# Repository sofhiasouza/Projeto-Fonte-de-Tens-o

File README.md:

# Projeto Fonte de Tensão - Eletrônica para Computação - BCC 020 - ICMC- USP

Grupo:
 - [Ana Vitória Gouvea](mailto:anavitoria_gouvea@usp.br)
 - [Eduardo Amaral](https://rolimans.dev)
 - [Matheus Luis Oliveira](mailto:matheuslos@usp.br)
 - [Sofhia de Souza](mailto:sofhiasouza@usp.br)

Turma: 
    BCC 020

Disciplina:
    SSC0180 - Eletrônica para Computação

Docente responsável:
    Eduardo do Valle Simões

# Vídeo de apresentação do projeto:

# Lista de componentes do circuito:

- 1x  [Transformador Trafo 24V 1A - 110/220VAC](https://www.baudaeletronica.com.br/transformador-trafo-1a-24v.html)
- 4x [Diodo 1N4004](https://www.baudaeletronica.com.br/diodo-1n4004.html) (Ponte de diodos retificadora / MAX 400V - 1A)
- 1x [Capacitor 220uF - 35 V](https://www.baudaeletronica.com.br/capacitor-eletrolitico-220uf-35v.html)
- 1x [Led Azul](https://www.baudaeletronica.com.br/led-de-alto-brilho-azul.html) (Gastará aprox 5mA)
- 2x [Resistor 2k2](https://www.baudaeletronica.com.br/resistor-2k2-5-1-4w.html) (Fica em série com o LED e o - Potênciometro)
- 1x [Diodo Zener 13V - 0.5W](https://www.baudaeletronica.com.br/diodo-zener-bzx55c-13v-0-5w.html) (Recebe no máximo 0.3W)
- 1x [Resistor 2k](https://www.baudaeletronica.com.br/resistor-2k-5-1-4w.html) (Fica em série com o Zener)
- 1x [Potênciometro 5K](https://www.baudaeletronica.com.br/potenciometro-linear-de-5k-5000.html)
- 1x [Transistor NPN BC337](https://www.baudaeletronica.com.br/transistor-npn-bc337.html)
- 1x [Switch](https://www.baudaeletronica.com.br/chave-alavanca-mrs-101n-amarela-com-neon.html)

# Simulação do Circuito no simulador Falstad:

- Acesse o simulador [Falstad](https://falstad.com/circuit/circuitjs.html)
- Vá em `File > Import from Text` e cole o conteúdo do arquivo `./circuitoFalstad.txt` presente neste repositório.

A simulação aberta deve ser semelhante a esta:

# Esquemático do Circuito no software CAD Eagle:
 - Obtenha o software [Eagle](https://www.autodesk.com/products/eagle/blog/how-to-install-autodesk-eagle-on-windows-mac-and-linux/)
 - Vá em `File > Open > Schematic...` e selecione o arquivo `./EagleFiles/fonte_simoes.sch` presente neste repositório.

O esquemático aberto deve ser semelhante a este:

# PCB   do Circuito no software CAD Eagle:
 - Obtenha o software [Eagle](https://www.autodesk.com/products/eagle/blog/how-to-install-autodesk-eagle-on-windows-mac-and-linux/)
 - Vá em `File > Open > Board...` e selecione o arquivo `./EagleFiles/fonte_simoes.brd` presente neste repositório.

O PCB aberto deve ser semelhante a este:

# Licença
Este projeto é livre; você pode redistribuí-lo e/ou modificá-lo sobre os termos da GNU General Public License publicada pela Free Software Foundation; versão 3 ou superior.

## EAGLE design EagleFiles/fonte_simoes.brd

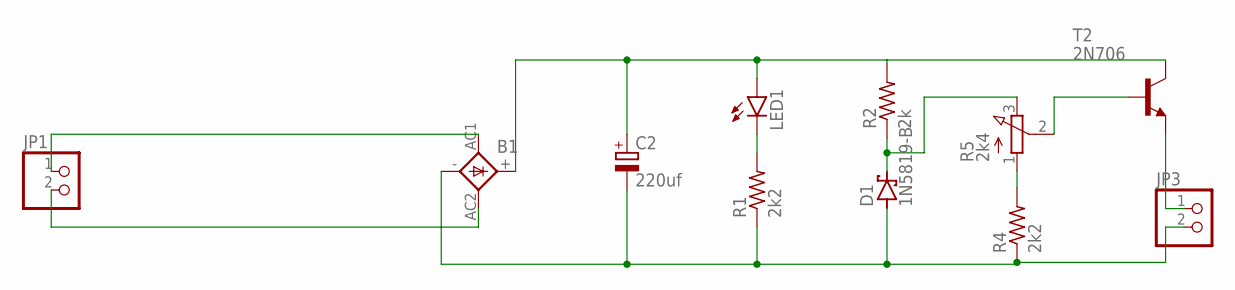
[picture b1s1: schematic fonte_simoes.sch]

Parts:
B1: 1KAB
C2: 220uf; TT5D10
D1: 1N5819-B; DO41-7.6
JP1, JP3: PINHD-1X2; 1X02
LED1: LED5MM
R1, R4: 2k2; 0309/12
R2: 2k; 0309/12
R5: 2k4; 3RP/1610N
T2: 2N706; TO18

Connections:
unnamed: B1.AC1, JP1.1
unnamed: B1.AC2, JP1.2
unnamed: B1.+, C2.+, LED1.A, R2.2, T2.3 (C)
unnamed: B1.-, C2.-, D1.A, JP3.2, R1.1, R4.1
unnamed: LED1.K (C), R1.2
unnamed: D1.C, R2.1, R5.3 (E)
unnamed: R5.2 (S), T2.2 (B)
unnamed: R4.2, R5.1 (A)
unnamed: JP3.1, T2.1 (E)

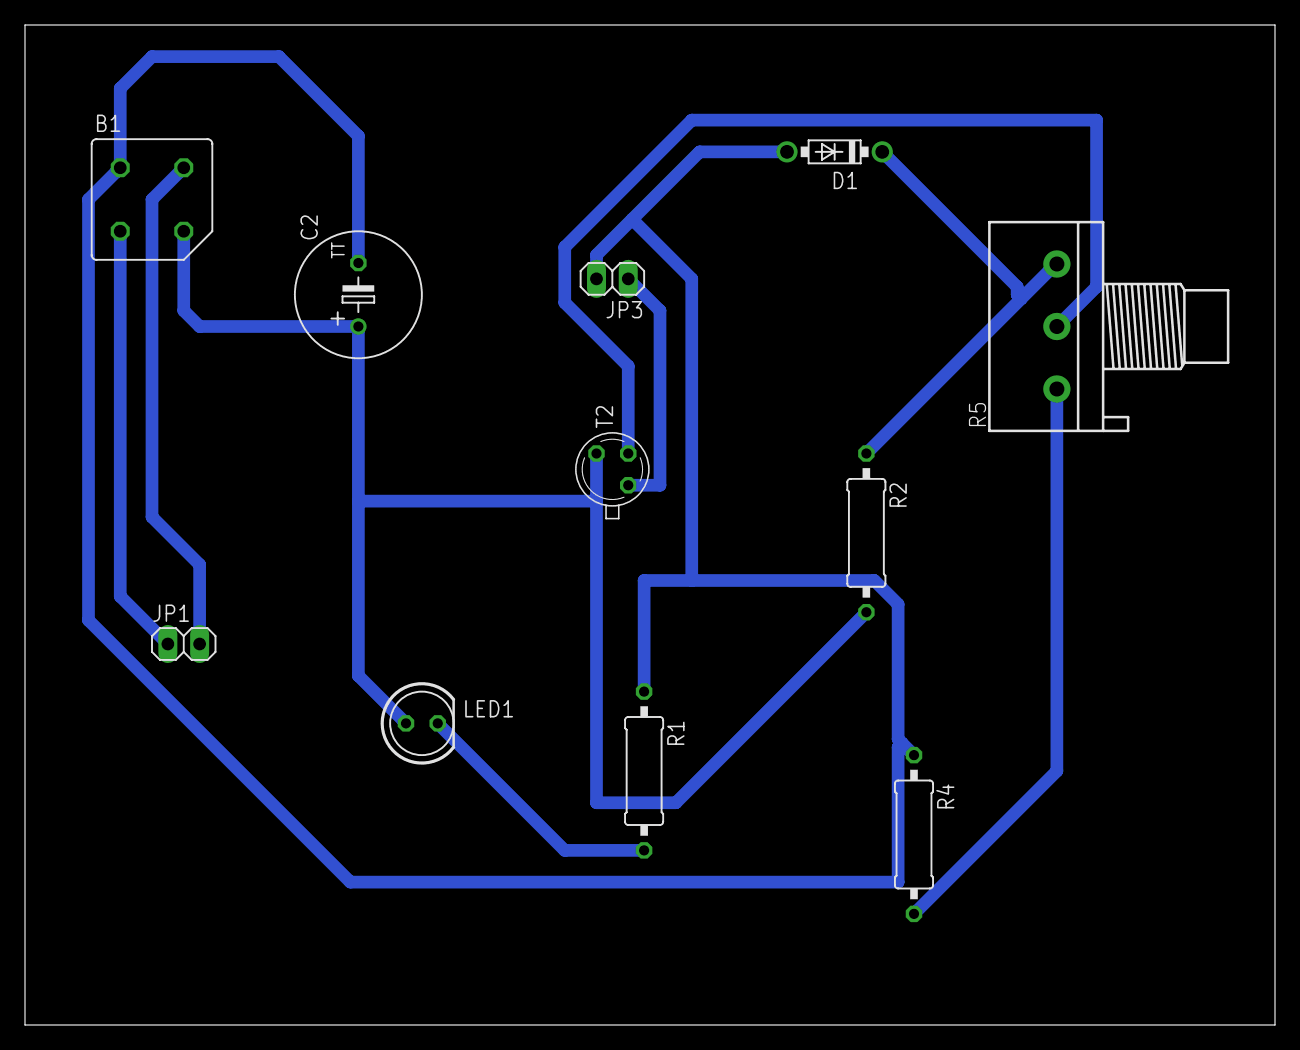
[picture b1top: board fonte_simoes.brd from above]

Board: 2 copper layers, 100.0 x 80.0 mm, 11 parts (0 on the bottom side), 9 nets.

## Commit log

2020-06-10 Inicio do projeto - Lista de COmponentes
2020-06-10 Circuito Falstad Adicionado
2020-06-11 Atualizado tutorial e circuito falstad
2020-06-11 Atualizado imagem PCB
2020-06-11 Licensa GPL 3 Adicionada
2020-06-11 Correções ortográficas
2020-06-11 Adicao licensa no readme
2020-06-11 Esquematico > PCB
2020-06-12 Vídeo adicionado
2020-06-12 Correção Link Vídeo
